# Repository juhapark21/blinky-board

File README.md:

# blinky-board
Blinky board made through Hack Club's Stasis! I made it because I saw it on #stasis-sisters and I wanted to make a shiny bird-shaped thing. I learned how to create a PCB from start to finish with this project. 

It's shaped like a duck! 

I followed [this tutorial](https://stasis.hackclub.com/starter-projects/blinky#blinky-board). 

[Link to project here](https://stasis.hackclub.com/dashboard/projects/cmnr3zax0012301mpaw86ej3r) 

### BoM
| Name              | Purpose                                       | Quantity | Total Cost (USD) | Link                                                                                                                                 | Distributor |
|-------------------|-----------------------------------------------|----------|------------------|--------------------------------------------------------------------------------------------------------------------------------------|-------------|
| PCB               | The thing to put it all on                    | 1        | 2.00             | https://cart.jlcpcb.com/quote?stencilLayer=2&stencilWidth=100&stencilLength=100&stencilCounts=5&plateType=1&spm=Jlcpcb.Homepage.1010 | jlcpcb      |
| LED               | Lights up!                                    | 10       | 1.40             | https://www.digikey.com/en/products/detail/liteon/LTL-4231N/214440                                                                   | Digikey     |
| Resistor (1kohm)  | Resist current flow of RV                     | 1        | 0.10             | https://www.digikey.com/en/products/detail/stackpole-electronics-inc/CF14JT1K00/1741314                                              | Digikey     |
| R (470ohm)        | Resist current flow of LEDs                   | 1        | 0.10             | https://www.digikey.com/en/products/detail/stackpole-electronics-inc/CF14JT470R/1741440                                              | Digikey     |
| RV                | Control speed of flashes                      | 1        | 2.60             | https://www.digikey.com/en/products/detail/tt-electronics-bi/P091S-FC20BR10K/2408860                                                 | Digikey     |
| C (1uF)           | Hold electrical energy for trigger            |          | 0.10             | https://www.digikey.com/en/products/detail/w%C3%BCrth-elektronik/860020672005/5727088                                                | Digikey     |
| Conn_01x01_Socket | To power my circuit/debug                     |          | 0.61             | https://www.digikey.com/en/products/detail/samtec-inc/TS-101-G-AA/6691609                                                            | Digikey     |
| Conn_01x02_Socket | To power my circuit/debug                     | 1        | 0.10             | https://www.digikey.com/en/products/detail/harwin-inc/M50-3530242/7044013                                                            | Digikey     |
| CD4017            | Controls LED blinking based on input from 555 | 1        | 0.96             | https://www.digikey.com/en/products/detail/texas-instruments/CD40175BE/528407                                                        | Digikey     |
| NE555P            | Clock for the blinky                          | 1        | 0.51             | https://www.digikey.com/en/products/detail/texas-instruments/NE555P/277057                                                           | Digikey     |

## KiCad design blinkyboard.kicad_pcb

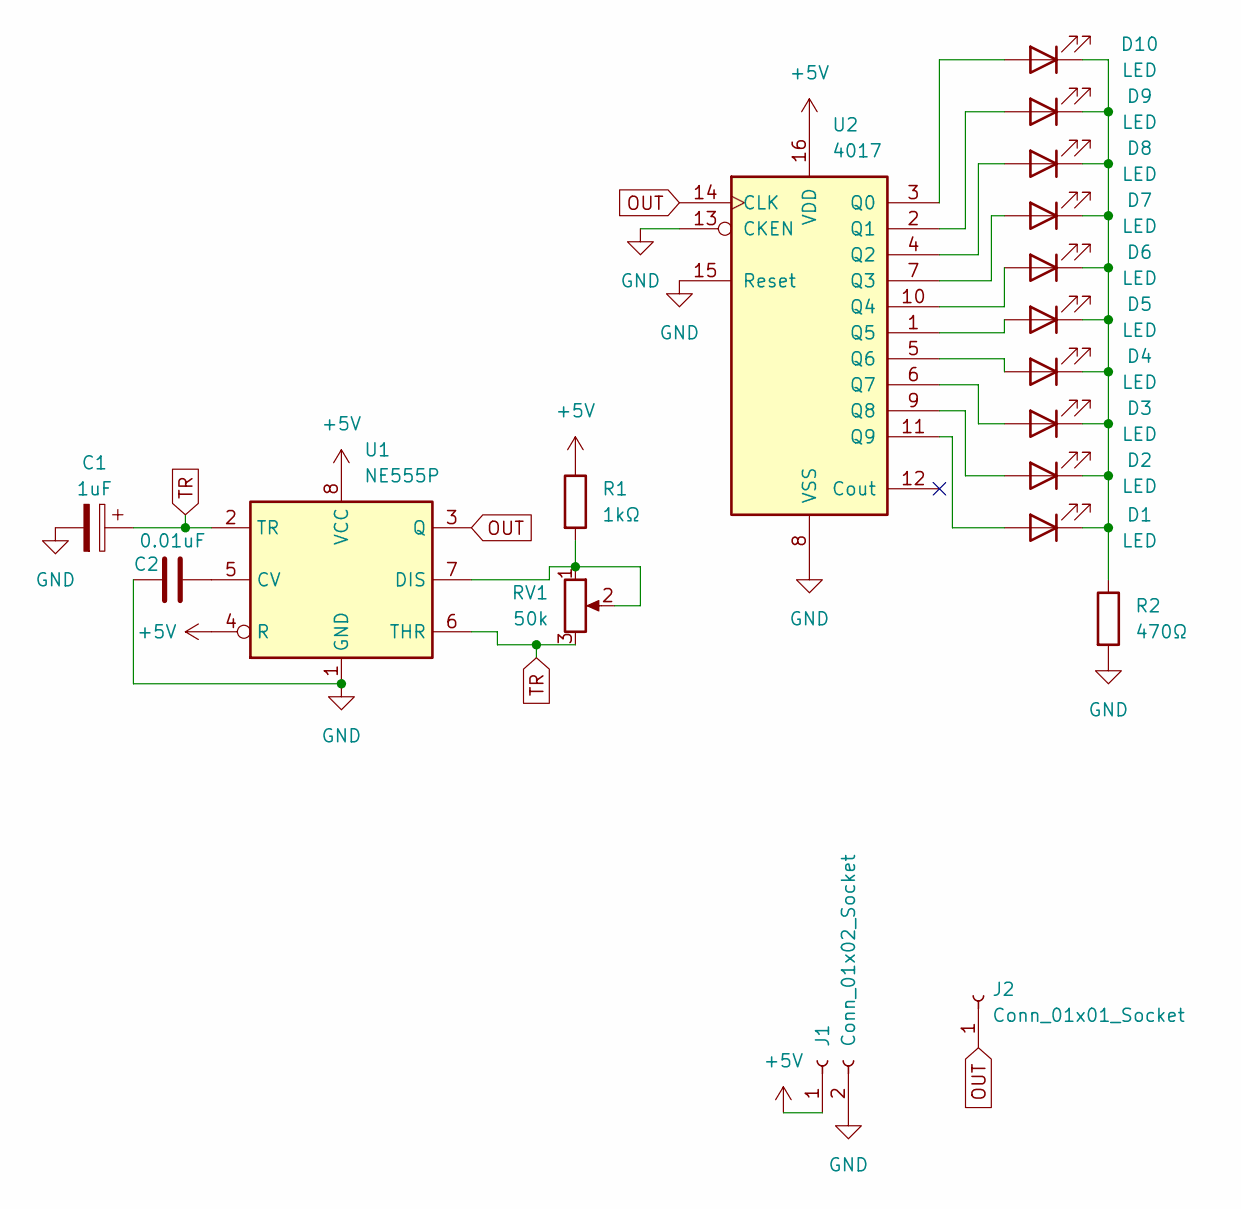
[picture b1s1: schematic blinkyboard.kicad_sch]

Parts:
C1: 1uF; CP_Radial_D5.0mm_P2.00mm
C2: 0.01uF; C_Disc_D7.5mm_W2.5mm_P5.00mm
D1, D2, D3, D4, D5, D6, D7, D8, D9, D10: LED; LED_D3.0mm
J1: Conn_01x02_Socket; PinHeader_1x02_P2.54mm_Vertical
J2: Conn_01x01_Socket; PinHeader_1x01_P2.54mm_Vertical
R1: 1kΩ; R_Axial_DIN0207_L6.3mm_D2.5mm_P7.62mm_Horizontal
R2: 470Ω; R_Axial_DIN0207_L6.3mm_D2.5mm_P7.62mm_Horizontal
RV1: 50k; Potentiometer_Vishay_T93YA_Vertical
U1: NE555P; DIP-8_W7.62mm
U2: 4017; N16

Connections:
+5V: J1.1, R1.1, U1.4 (R), U1.8 (VCC), U2.16 (VDD)
GND: C1.2, C2.1, J1.2, R2.2, U1.1 (GND), U2.8 (VSS), U2.13 (CKEN), U2.15 (Reset)
unnamed: D1.2 (A), U2.11 (Q9)
unnamed: D1.1 (K), D2.1 (K), D3.1 (K), D4.1 (K), D5.1 (K), D6.1 (K), D7.1 (K), D8.1 (K), D9.1 (K), D10.1 (K), R2.1
unnamed: D2.2 (A), U2.9 (Q8)
unnamed: D3.2 (A), U2.6 (Q7)
unnamed: D4.2 (A), U2.5 (Q6)
unnamed: D5.2 (A), U2.1 (Q5)
unnamed: D6.2 (A), U2.10 (Q4)
unnamed: D7.2 (A), U2.7 (Q3)
unnamed: D8.2 (A), U2.4 (Q2)
unnamed: D9.2 (A), U2.2 (Q1)
unnamed: D10.2 (A), U2.3 (Q0)
unnamed: C2.2, U1.5 (CV)
unnamed: R1.2, RV1.1, RV1.2, U1.7 (DIS)
OUT: J2.1, U1.3 (Q), U2.14 (CLK)
TR: C1.1, RV1.3, U1.2 (TR), U1.6 (THR)

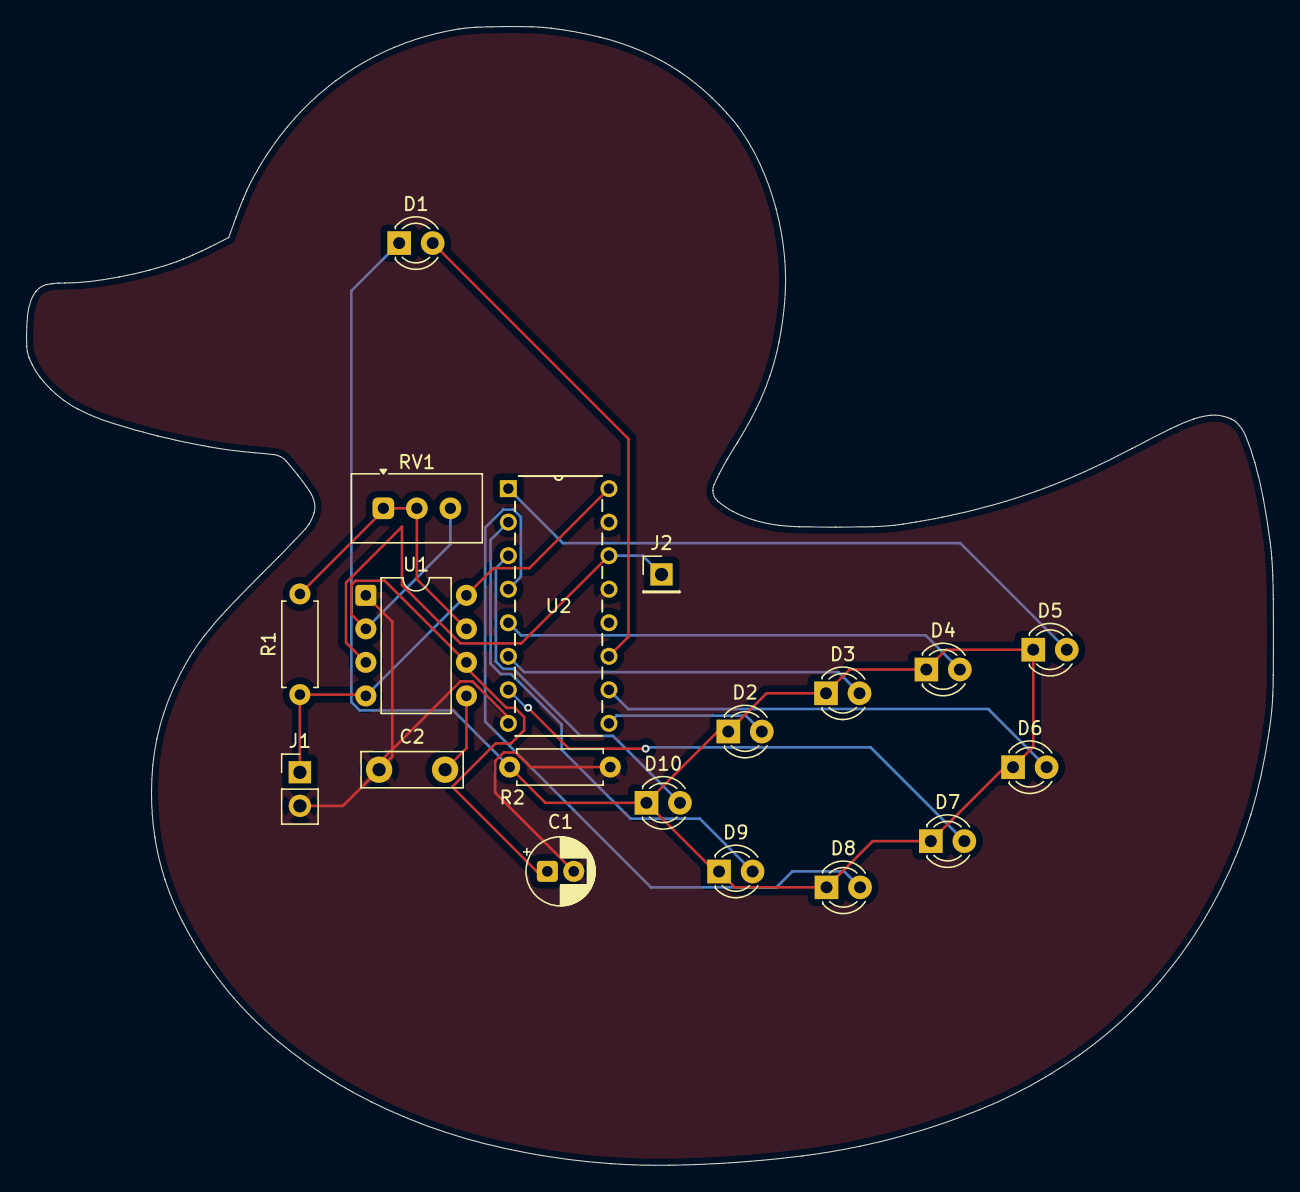
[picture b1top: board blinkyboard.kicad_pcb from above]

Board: 2 copper layers, 94.4 x 86.3 mm, 19 parts (0 on the bottom side), 17 nets.

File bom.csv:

Name,Purpose,Quantity,Total Cost (USD),Link,Distributor
"PCB","The thing to put it all on",1,2.00,"https://cart.jlcpcb.com/quote?stencilLayer=2&stencilWidth=10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","jlcpcb"
"LED","Lights up!",10,1.40,"https://www.digikey.com/en/products/detail/liteon/LTL-4231N/214440","Digikey"
"Resistor (1kohm)","Resist current flow of RV",1,0.10,"https://www.digikey.com/en/products/detail/stackpole-electro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","Digikey"
"R (470ohm)","Resist current flow of LEDs",1,0.10,"https://www.digikey.com/en/products/detail/stackpole-electro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","Digikey"
"RV","Control speed of flashes",1,2.60,"https://www.digikey.com/en/products/detail/tt-electronics-bi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","Digikey"
"C (1uF)","Hold electrical energy for trigger",,0.10,"https://www.digikey.com/en/products/detail/w%C3%BCrth-elektr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","Digikey"
"Conn_01x01_Socket","To power my circuit/debug",,0.61,"https://www.digikey.com/en/products/detail/samtec-inc/TS-101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","Digikey"
"Conn_01x02_Socket","To power my circuit/debug",1,0.10,"https://www.digikey.com/en/products/detail/harwin-inc/M50-35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","Digikey"
"CD4017","Controls LED blinking based on input from 555",1,0.96,"https://www.digikey.com/en/products/detail/texas-instruments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","Digikey"
"NE555P","Clock for the blinky",1,0.51,"https://www.digikey.com/en/products/detail/texas-instruments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","Digikey"

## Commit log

2026-06-12 Update README with image
    Added images and enhanced project description.
2026-06-12 Updated BOM
